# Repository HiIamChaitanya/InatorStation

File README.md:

# InatorStation  

Hey! This is my open-source soldering station design. This project marks my transition to open-source hardware.  InatorStation is designed to be versatile, repairable, and upgradable. It currently supports the T12 handle, with plans to expand compatibility to the JBC T210 handle in the future. The design files and firmware are fully open-source, allowing you to customize, repair, or upgrade the station to suit your needs. I mostly prefer 2 layer home-brewed PCB for repeatability, but later versions will use 4 layers due to complex design (upgrading handle and adding some sensors for precise work).

### Specifications  

| **Feature**               | **Details**                     |
|---------------------------|---------------------------------|
| **Power Supply**          | 24V, 4A                         |
| **Max Thermal Transfer**  | 80W                             |
| **Temperature Range**     | 200℃ - 400℃                     | 
| **Control**               | PID Auto-Tune                   |
| **Additional Features**   | Temperature Data Logging        |
| **Handle support          | T12 , T210                      |

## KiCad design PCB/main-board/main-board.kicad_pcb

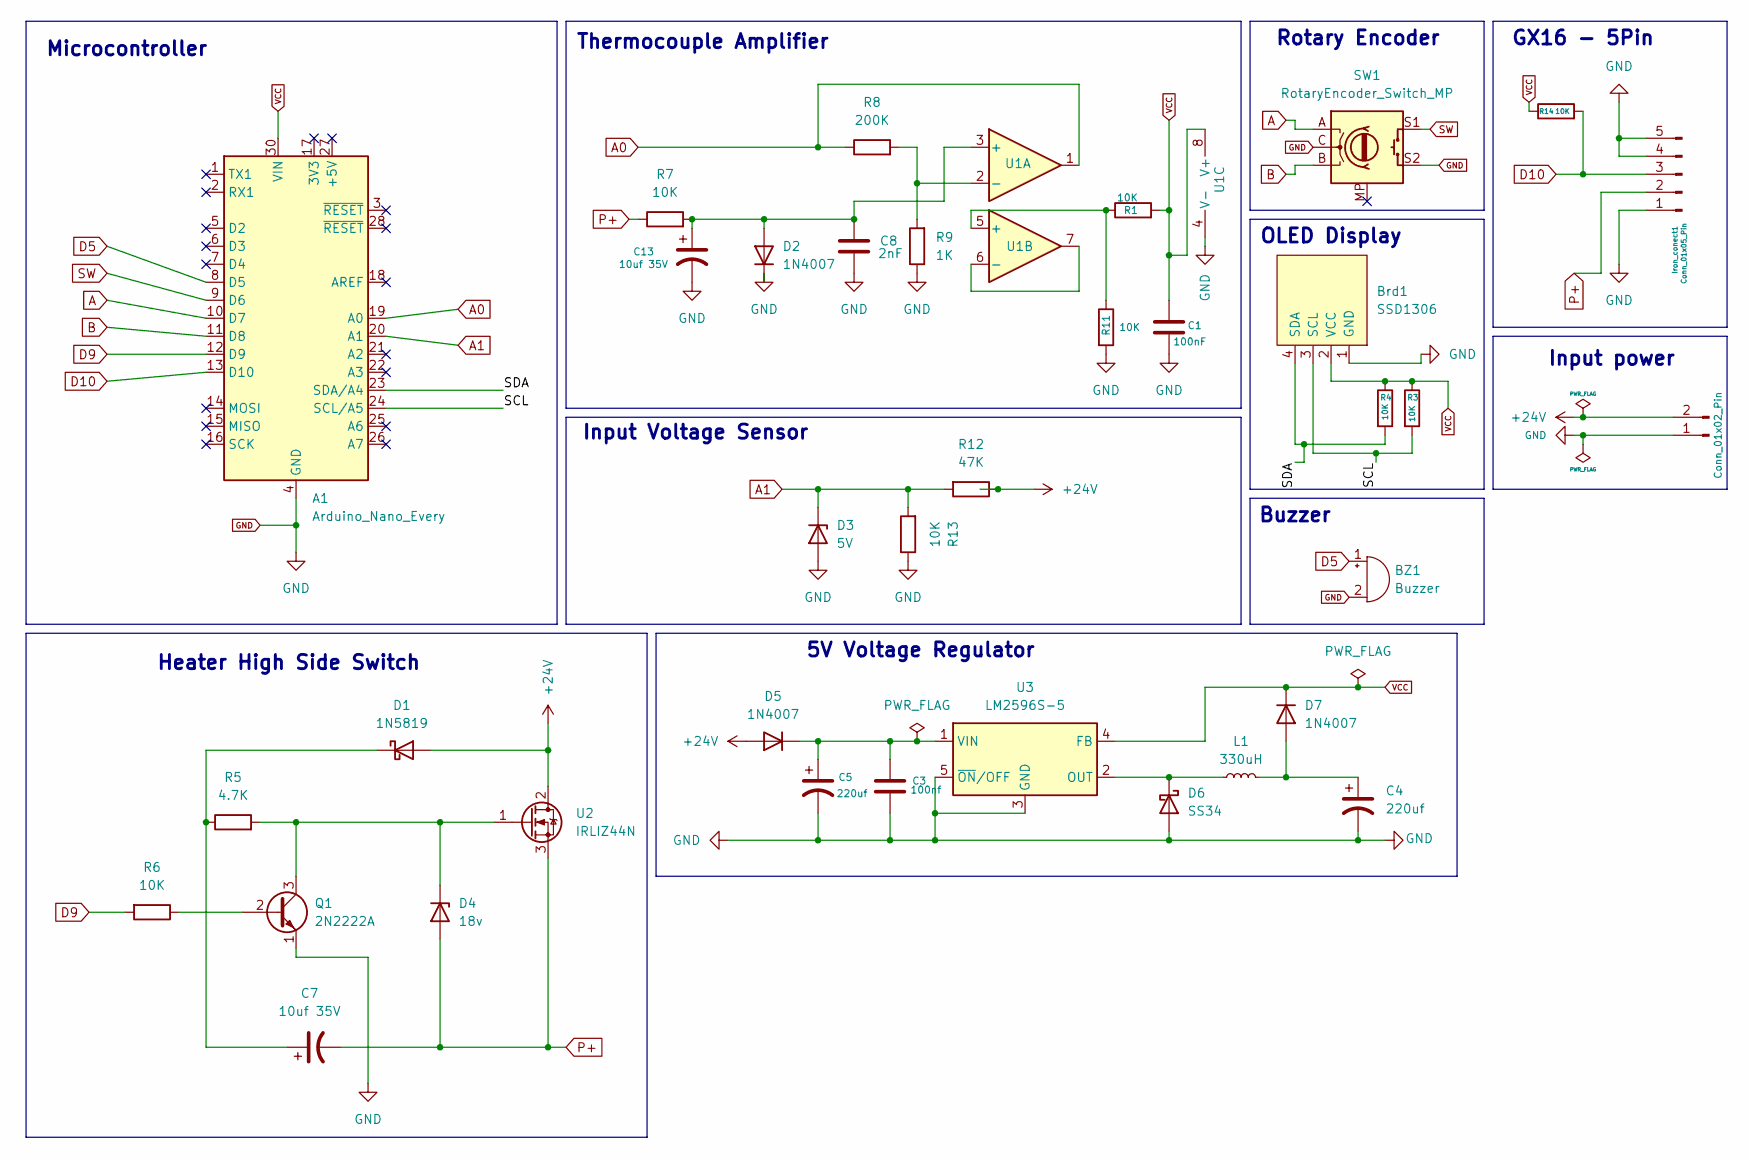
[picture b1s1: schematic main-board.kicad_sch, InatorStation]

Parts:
A1: Arduino_Nano_Every; Arduino_Nano
BZ1: Buzzer; Buzzer_12x9.5RM7.6
Brd1: SSD1306; 128x64OLED
C1: 100nF; C_1206_3216Metric
C3: 100nf; C_1206_3216Metric
C4, C5: 220uf; CP_Elec_8x10
C7, C13: 10uf 35V; CP_Elec_5x5.7
C8: 2nF; C_1206_3216Metric
D1: 1N5819; D_SOD-123
D2, D5, D7: 1N4007; D_SMA
D3: 5V; D_MicroMELF_Handsoldering
D4: 18v; D_MiniMELF_Handsoldering
D6: SS34; D_SMA
Iron_conect1: Conn_01x05_Pin; TerminalBlock_MetzConnect_Type101_RT01605HBWC_1x05_P5.08mm_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
J1: Conn_01x02_Pin; TerminalBlock_MetzConnect_Type101_RT01602HBWC_1x02_P5.08mm_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
L1: 330uH; L_Coilcraft_LPS4414
Q1: 2N2222A; SOT-23_Handsoldering
R1, R3, R4, R6, R7, R11, R13, R14: 10K; R_1206_3216Metric
R5: 4.7K; R_1206_3216Metric
R8: 200K; R_1206_3216Metric
R9: 1K; R_1206_3216Metric
R12: 47K; R_1206_3216Metric
SW1: RotaryEncoder_Switch_MP; RotaryEncoder_Alps_EC11E-Switch_Vertical_H20mm
U1: LM358; TSSOP-8_3x3mm_P0.65mm
U2: IRLIZ44N; TO-220F-3_Vertical
U3: LM2596S-5; TO-263-5_TabPin3

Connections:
+24V: D1.2 (A), D5.2 (A), J1.2, R12.1, U2.2 (D)
/SCL: A1.24 (SCL/A5), Brd1.3 (SCL), R3.2
/SDA: A1.23 (SDA/A4), Brd1.4 (SDA), R4.2
A: A1.10 (D7), SW1.A
A0: A1.19 (A0), R8.1, U1.1
A1: A1.20 (A1), D3.1 (K), R12.2, R13.2
B: A1.11 (D8), SW1.B
D5: A1.8 (D5), BZ1.1 (+)
D9: A1.12 (D9), R6.2
D10: A1.13 (D10), Iron_conect1.3, R14.2
GND: A1.4 (GND), A1.29 (GND), BZ1.2 (-), Brd1.1 (GND), C1.2, C3.2, C4.2, C5.2, C8.2, C13.2, D2.1 (K), D3.2 (A), D6.2 (A), Iron_conect1.1, Iron_conect1.4, Iron_conect1.5, J1.1, Q1.1 (E), R9.1, R11.2, R13.1, SW1.C, SW1.S2, U1.4 (V-), U3.3 (GND), U3.5 (~ON/OFF)
unnamed: C7.1, D1.1 (K), R5.1
unnamed: C8.1, C13.1, D2.2 (A), R7.2, U1.3 (+)
unnamed: D4.1 (K), Q1.3 (C), R5.2, U2.1 (G)
unnamed: C3.1, C5.1, D5.1 (K), U3.1 (VIN)
unnamed: D6.1 (K), L1.1, U3.2 (OUT)
unnamed: C4.1, D7.2 (A), L1.2
unnamed: Q1.2 (B), R6.1
unnamed: R8.2, R9.2, U1.2 (-)
unnamed: R1.1, R11.1, U1.5 (+)
unnamed: U1.6 (-), U1.7
P+: C7.2, D4.2 (A), Iron_conect1.2, R7.1, U2.3 (S)
SW: A1.9 (D6), SW1.S1
VCC: A1.30 (VIN), Brd1.2 (VCC), C1.1, D7.1 (K), R1.2, R3.1, R4.1, R14.1, U1.8 (V+), U3.4 (FB)

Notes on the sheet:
Rotary Encoder
Microcontroller
Thermocouple Amplifier
GX16 - 5Pin
OLED Display
Buzzer
Heater High Side Switch
5V Voltage Regulator
Input power
Input Voltage Sensor

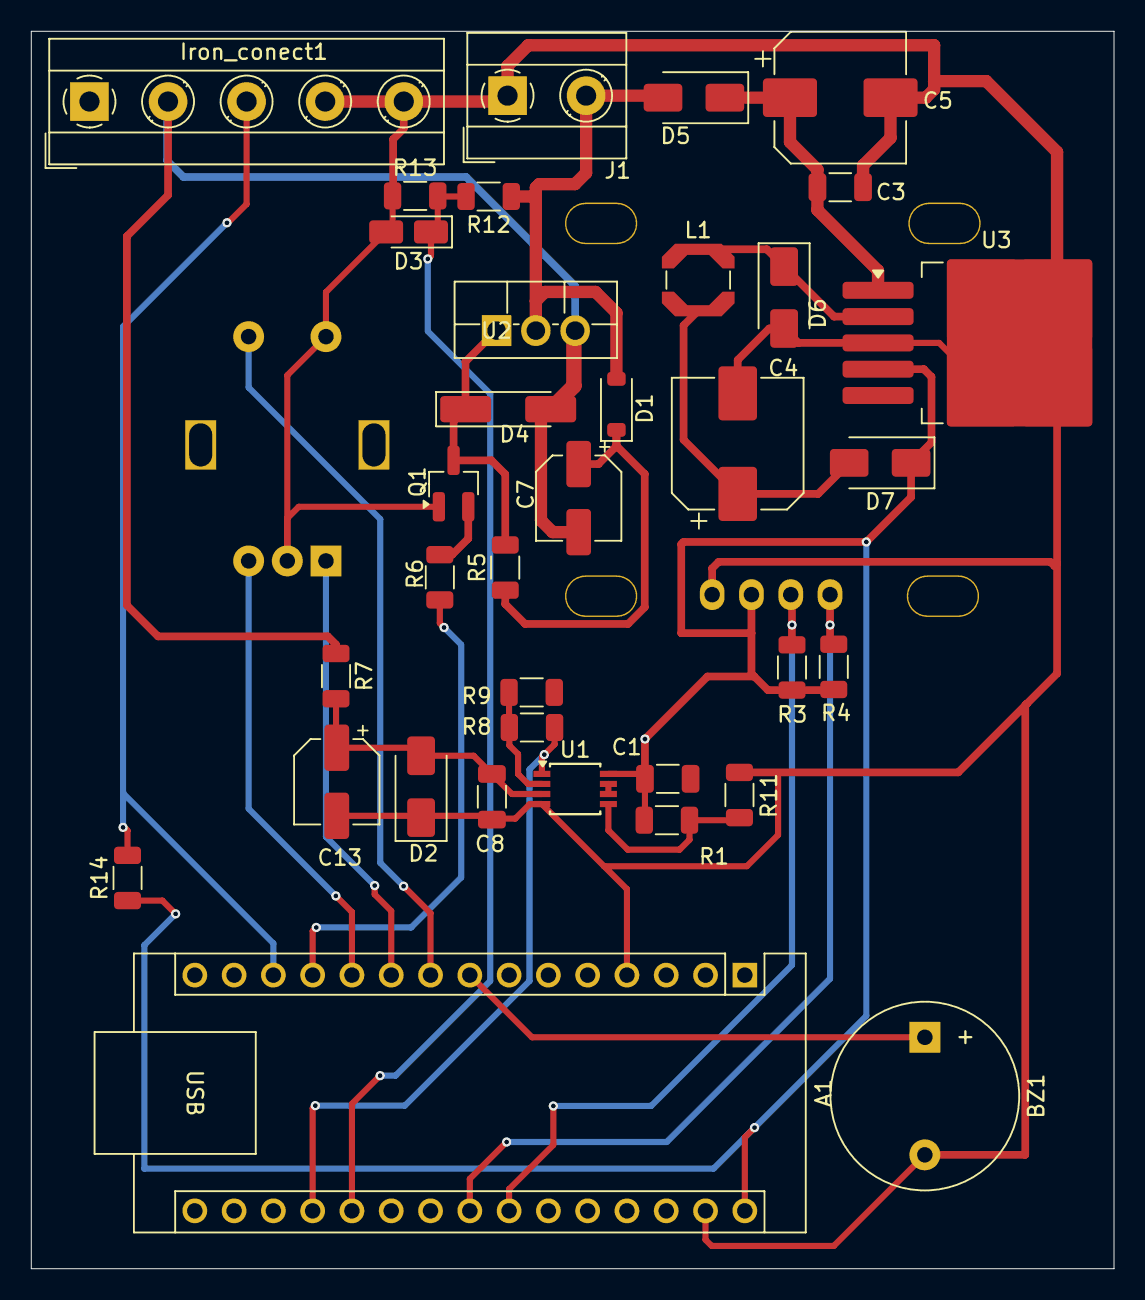
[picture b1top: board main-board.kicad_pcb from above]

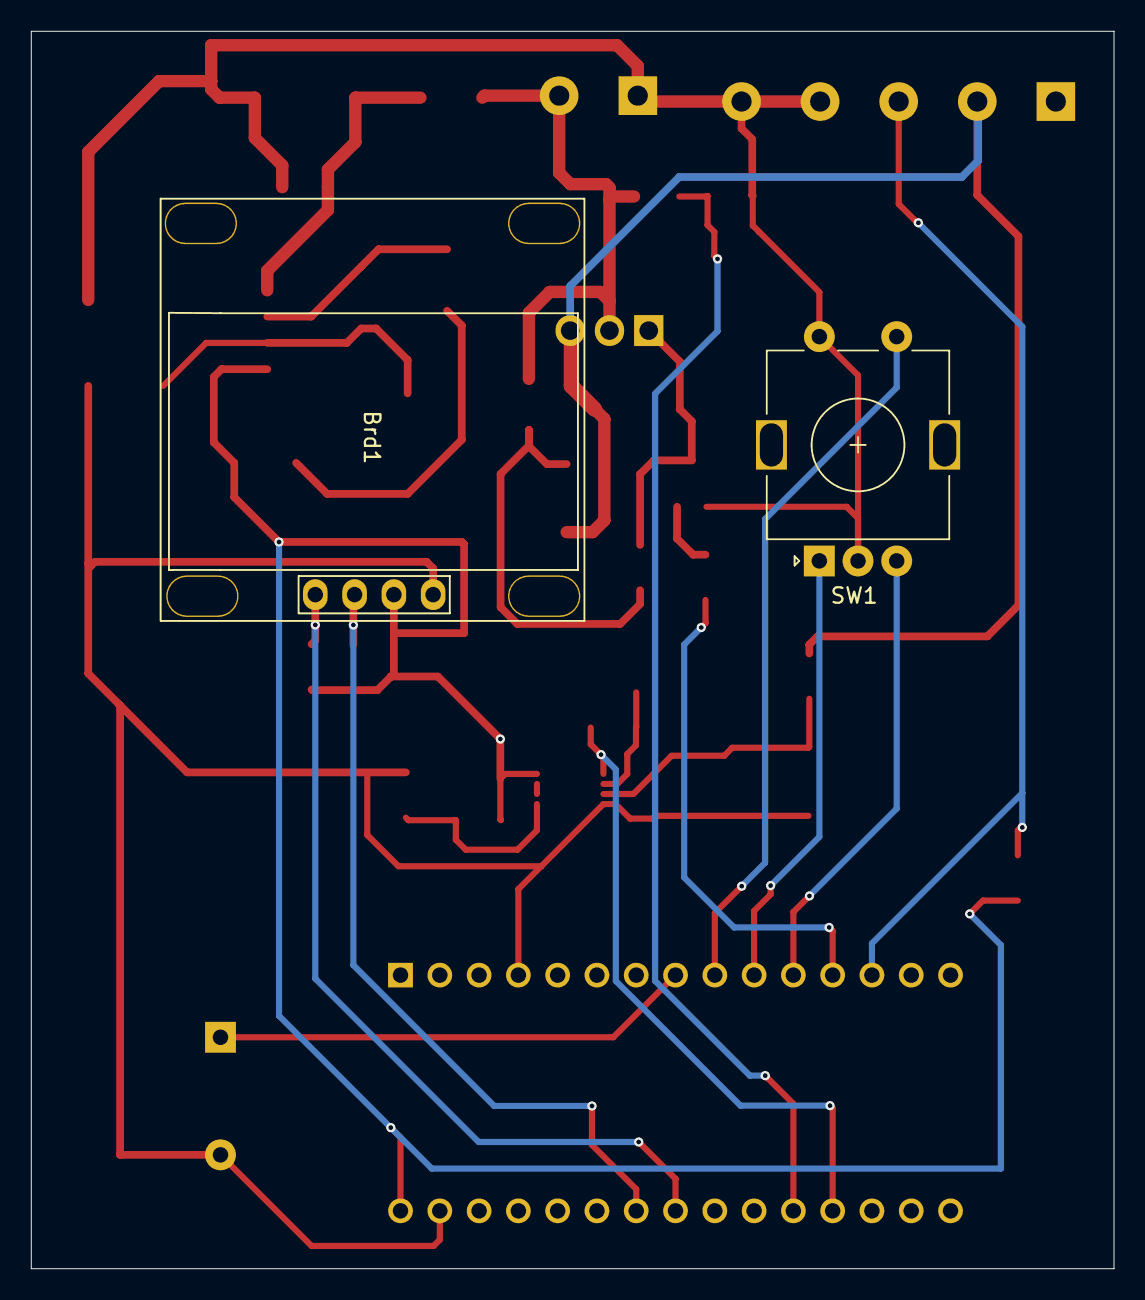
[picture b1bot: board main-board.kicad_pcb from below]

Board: 2 copper layers, 70.0 x 80.0 mm, 37 parts (2 on the bottom side), 24 nets.

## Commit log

2024-11-19 LICENSE.md
2024-12-20 updated KiCad files
2024-12-20 README.md update
2025-01-03 KiCad Project
2025-01-03 CAD-files
2025-01-03 init
2025-01-03 License
2025-01-04 setup script
2025-01-08 PCB files
2025-01-08 README
2025-01-08 setup file
2025-01-08 updated PCB files
2025-02-28 main
